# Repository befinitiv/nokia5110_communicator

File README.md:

# Contents

This repository contains Kicad PCB files and OpenSCAD mechanical parts to build a custom BLE keyboard.

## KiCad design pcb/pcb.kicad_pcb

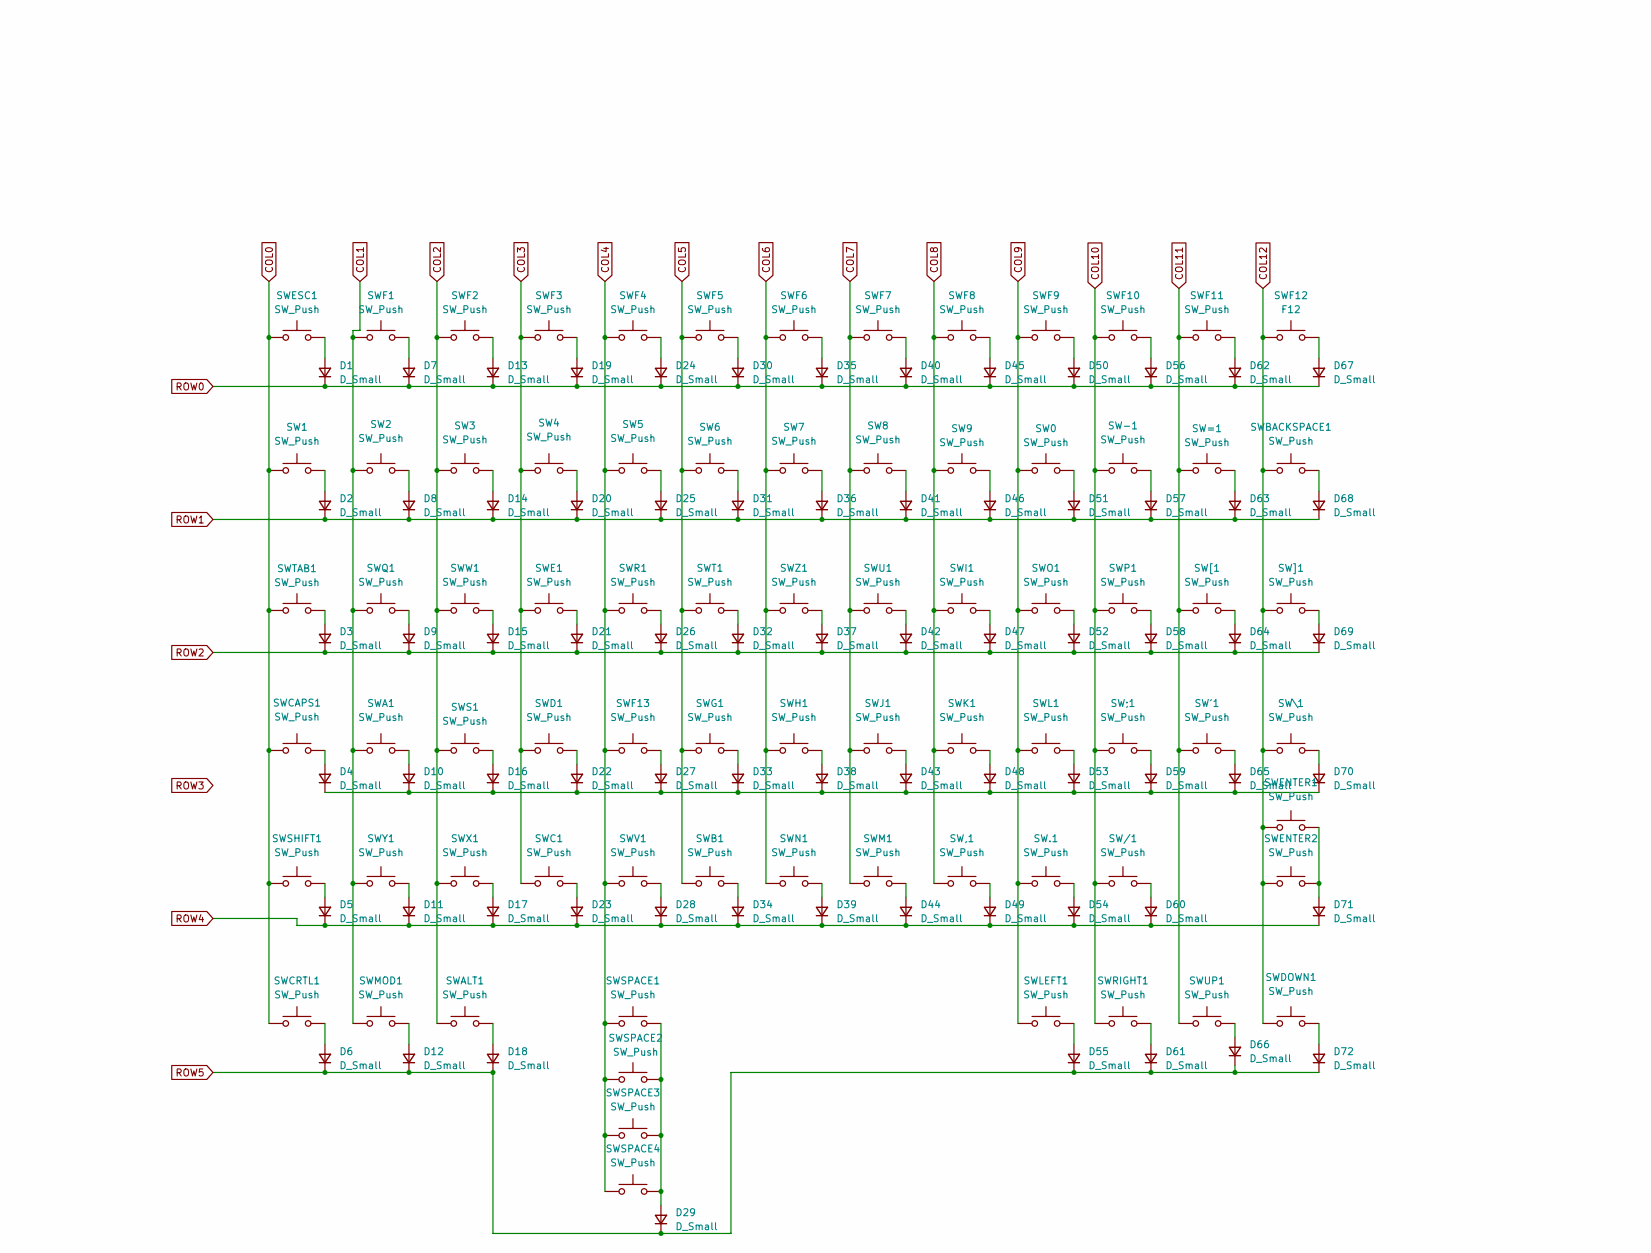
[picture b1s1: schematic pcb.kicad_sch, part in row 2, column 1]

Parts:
D1, D2, D3, D4, D5, D6, D7, D8, D9, D10, D11, D12, D13, D14, D15, D16, D17, D18, D19, D20, D21, D22, D23, D24, D25, D26, D27, D28, D29, D30, D31, D32, D33, D34, D35, D36, D37, D38, D39, D40, D41, D42, D43, D44, D45, D46, D47, D48, D49, D50, D51, D52, D53, D54, D55, D56, D57, D58, D59, D60, D61, D62, D63, D64, D65, D66, D67, D68, D69, D70, D71, D72: D_Small; D_0603_1608Metric_Pad1.05x0.95mm_HandSolder
SW0, SW1, SW2, SW3, SW4, SW5, SW6, SW7, SW8, SW9, SW.1: SW_Push; membrane_key
SW'1: SW_Push; membrane_key
SW,1: SW_Push; membrane_key
SW-1: SW_Push; membrane_key
SW/1: SW_Push; membrane_key
SW;1: SW_Push; membrane_key
SW=1: SW_Push; membrane_key
SWA1: SW_Push; membrane_key
SWALT1: SW_Push; membrane_key
SWB1: SW_Push; membrane_key
SWBACKSPACE1: SW_Push; membrane_key
SWC1: SW_Push; membrane_key
SWCAPS1: SW_Push; membrane_key
SWCRTL1: SW_Push; membrane_key
SWD1: SW_Push; membrane_key
SWDOWN1: SW_Push; membrane_key
SWE1: SW_Push; membrane_key
SWENTER1, SWENTER2: SW_Push; membrane_key
SWESC1: SW_Push; membrane_key
SWF1, SWF2, SWF3, SWF4, SWF5, SWF6, SWF7, SWF8, SWF9, SWF10, SWF11, SWF13: SW_Push; membrane_key
SWF12: F12; membrane_key
SWG1: SW_Push; membrane_key
SWH1: SW_Push; membrane_key
SWI1: SW_Push; membrane_key
SWJ1: SW_Push; membrane_key
SWK1: SW_Push; membrane_key
SWL1: SW_Push; membrane_key
SWLEFT1: SW_Push; membrane_key
SWM1: SW_Push; membrane_key
SWMOD1: SW_Push; membrane_key
SWN1: SW_Push; membrane_key
SWO1: SW_Push; membrane_key
SWP1: SW_Push; membrane_key
SWQ1: SW_Push; membrane_key
SWR1: SW_Push; membrane_key
SWRIGHT1: SW_Push; membrane_key
SWS1: SW_Push; membrane_key
SWSHIFT1: SW_Push; membrane_key
SWSPACE1, SWSPACE2, SWSPACE3, SWSPACE4: SW_Push; membrane_key
SWT1: SW_Push; membrane_key
SWTAB1: SW_Push; membrane_key
SWU1: SW_Push; membrane_key
SWUP1: SW_Push; membrane_key
SWV1: SW_Push; membrane_key
SWW1: SW_Push; membrane_key
SWX1: SW_Push; membrane_key
SWY1: SW_Push; membrane_key
SWZ1: SW_Push; membrane_key
SW[1: SW_Push; membrane_key
SW\1: SW_Push; membrane_key
SW]1: SW_Push; membrane_key

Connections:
COL0: SW1.1, SWCAPS1.1, SWCRTL1.1, SWESC1.1, SWSHIFT1.1, SWTAB1.1; also elsewhere on the board
COL1: SW2.1, SWA1.1, SWF1.1, SWMOD1.1, SWQ1.1, SWY1.1; also elsewhere on the board
COL2: SW3.1, SWALT1.1, SWF2.1, SWS1.1, SWW1.1, SWX1.1; also elsewhere on the board
COL3: SW4.1, SWC1.1, SWD1.1, SWE1.1, SWF3.1; also elsewhere on the board
COL4: SW5.1, SWF4.1, SWF13.1, SWR1.1, SWSPACE1.1, SWSPACE2.1, SWSPACE3.1, SWSPACE4.1, SWV1.1; also elsewhere on the board
COL5: SW6.1, SWB1.1, SWF5.1, SWG1.1, SWT1.1; also elsewhere on the board
COL6: SW7.1, SWF6.1, SWH1.1, SWN1.1, SWZ1.1; also elsewhere on the board
COL7: SW8.1, SWF7.1, SWJ1.1, SWM1.1, SWU1.1; also elsewhere on the board
COL8: SW9.1, SW,1.1, SWF8.1, SWI1.1, SWK1.1; also elsewhere on the board
COL9: SW0.1, SW.1.1, SWF9.1, SWL1.1, SWLEFT1.1, SWO1.1; also elsewhere on the board
COL10: SW-1.1, SW/1.1, SW;1.1, SWF10.1, SWP1.1, SWRIGHT1.1; also elsewhere on the board
COL11: SW'1.1, SW=1.1, SWF11.1, SWUP1.1, SW[1.1; also elsewhere on the board
COL12: SWBACKSPACE1.1, SWDOWN1.1, SWENTER1.1, SWENTER2.1, SWF12.1, SW\1.1, SW]1.1; also elsewhere on the board
unnamed: D4.1 (K), D10.1 (K), D16.1 (K), D22.1 (K), D27.1 (K), D33.1 (K), D38.1 (K), D43.1 (K), D48.1 (K), D53.1 (K), D59.1 (K), D65.1 (K), D70.1 (K)
unnamed: D51.2 (A), SW0.2
unnamed: D2.2 (A), SW1.2
unnamed: D8.2 (A), SW2.2
unnamed: D14.2 (A), SW3.2
unnamed: D20.2 (A), SW4.2
unnamed: D25.2 (A), SW5.2
unnamed: D31.2 (A), SW6.2
unnamed: D36.2 (A), SW7.2
unnamed: D41.2 (A), SW8.2
unnamed: D46.2 (A), SW9.2
unnamed: D65.2 (A), SW'1.2
unnamed: D49.2 (A), SW,1.2
unnamed: D57.2 (A), SW-1.2
unnamed: D54.2 (A), SW.1.2
unnamed: D60.2 (A), SW/1.2
unnamed: D59.2 (A), SW;1.2
unnamed: D63.2 (A), SW=1.2
unnamed: D10.2 (A), SWA1.2
unnamed: D18.2 (A), SWALT1.2
unnamed: D34.2 (A), SWB1.2
unnamed: D68.2 (A), SWBACKSPACE1.2
unnamed: D23.2 (A), SWC1.2
unnamed: D4.2 (A), SWCAPS1.2
unnamed: D6.2 (A), SWCRTL1.2
unnamed: D22.2 (A), SWD1.2
unnamed: D72.2 (A), SWDOWN1.2
unnamed: D21.2 (A), SWE1.2
unnamed: D71.2 (A), SWENTER1.2, SWENTER2.2
unnamed: D1.2 (A), SWESC1.2
unnamed: D7.2 (A), SWF1.2
unnamed: D13.2 (A), SWF2.2
unnamed: D19.2 (A), SWF3.2
unnamed: D24.2 (A), SWF4.2
unnamed: D30.2 (A), SWF5.2
unnamed: D35.2 (A), SWF6.2
unnamed: D40.2 (A), SWF7.2
unnamed: D45.2 (A), SWF8.2
unnamed: D50.2 (A), SWF9.2
unnamed: D56.2 (A), SWF10.2
unnamed: D62.2 (A), SWF11.2
unnamed: D67.2 (A), SWF12.2
unnamed: D27.2 (A), SWF13.2
unnamed: D33.2 (A), SWG1.2
unnamed: D38.2 (A), SWH1.2
unnamed: D47.2 (A), SWI1.2
unnamed: D43.2 (A), SWJ1.2
unnamed: D48.2 (A), SWK1.2
unnamed: D53.2 (A), SWL1.2
unnamed: D55.2 (A), SWLEFT1.2
unnamed: D44.2 (A), SWM1.2
unnamed: D12.2 (A), SWMOD1.2
unnamed: D39.2 (A), SWN1.2
unnamed: D52.2 (A), SWO1.2
unnamed: D58.2 (A), SWP1.2
unnamed: D9.2 (A), SWQ1.2
unnamed: D26.2 (A), SWR1.2
unnamed: D61.2 (A), SWRIGHT1.2
unnamed: D16.2 (A), SWS1.2
unnamed: D5.2 (A), SWSHIFT1.2
unnamed: D29.2 (A), SWSPACE1.2, SWSPACE2.2, SWSPACE3.2, SWSPACE4.2
unnamed: D32.2 (A), SWT1.2
unnamed: D3.2 (A), SWTAB1.2
unnamed: D42.2 (A), SWU1.2
unnamed: D66.2 (A), SWUP1.2
unnamed: D28.2 (A), SWV1.2
unnamed: D15.2 (A), SWW1.2
unnamed: D17.2 (A), SWX1.2
unnamed: D11.2 (A), SWY1.2
unnamed: D37.2 (A), SWZ1.2
unnamed: D64.2 (A), SW[1.2
unnamed: D70.2 (A), SW\1.2
unnamed: D69.2 (A), SW]1.2
ROW0: D1.1 (K), D7.1 (K), D13.1 (K), D19.1 (K), D24.1 (K), D30.1 (K), D35.1 (K), D40.1 (K), D45.1 (K), D50.1 (K), D56.1 (K), D62.1 (K), D67.1 (K); also elsewhere on the board
ROW1: D2.1 (K), D8.1 (K), D14.1 (K), D20.1 (K), D25.1 (K), D31.1 (K), D36.1 (K), D41.1 (K), D46.1 (K), D51.1 (K), D57.1 (K), D63.1 (K), D68.1 (K); also elsewhere on the board
ROW2: D3.1 (K), D9.1 (K), D15.1 (K), D21.1 (K), D26.1 (K), D32.1 (K), D37.1 (K), D42.1 (K), D47.1 (K), D52.1 (K), D58.1 (K), D64.1 (K), D69.1 (K); also elsewhere on the board
ROW4: D5.1 (K), D11.1 (K), D17.1 (K), D23.1 (K), D28.1 (K), D34.1 (K), D39.1 (K), D44.1 (K), D49.1 (K), D54.1 (K), D60.1 (K), D71.1 (K); also elsewhere on the board
ROW5: D6.1 (K), D12.1 (K), D18.1 (K), D29.1 (K), D55.1 (K), D61.1 (K), D66.1 (K), D72.1 (K); also elsewhere on the board

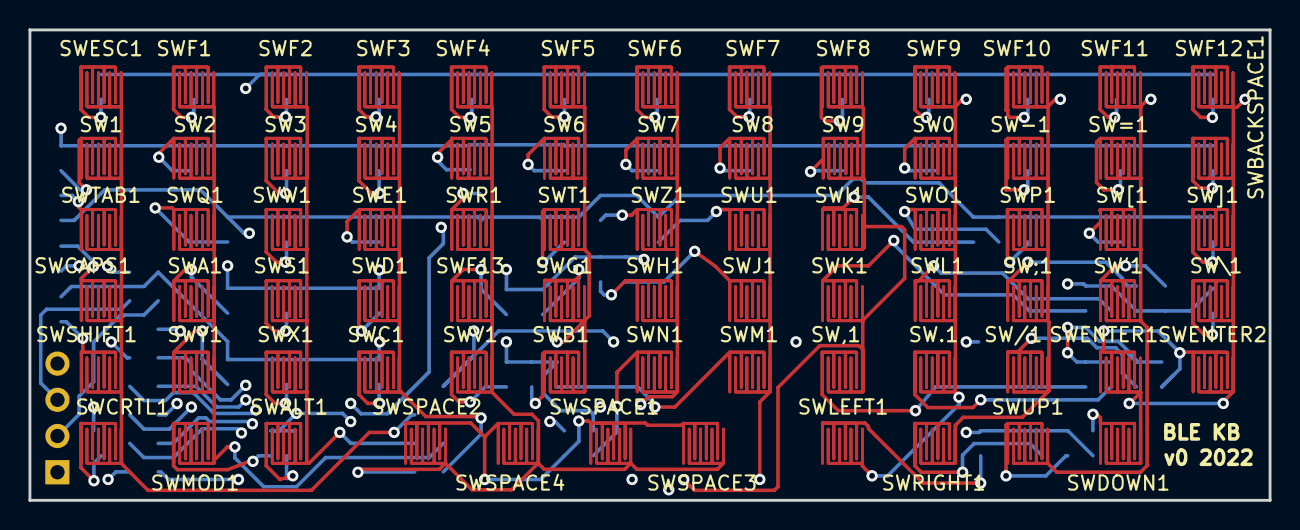
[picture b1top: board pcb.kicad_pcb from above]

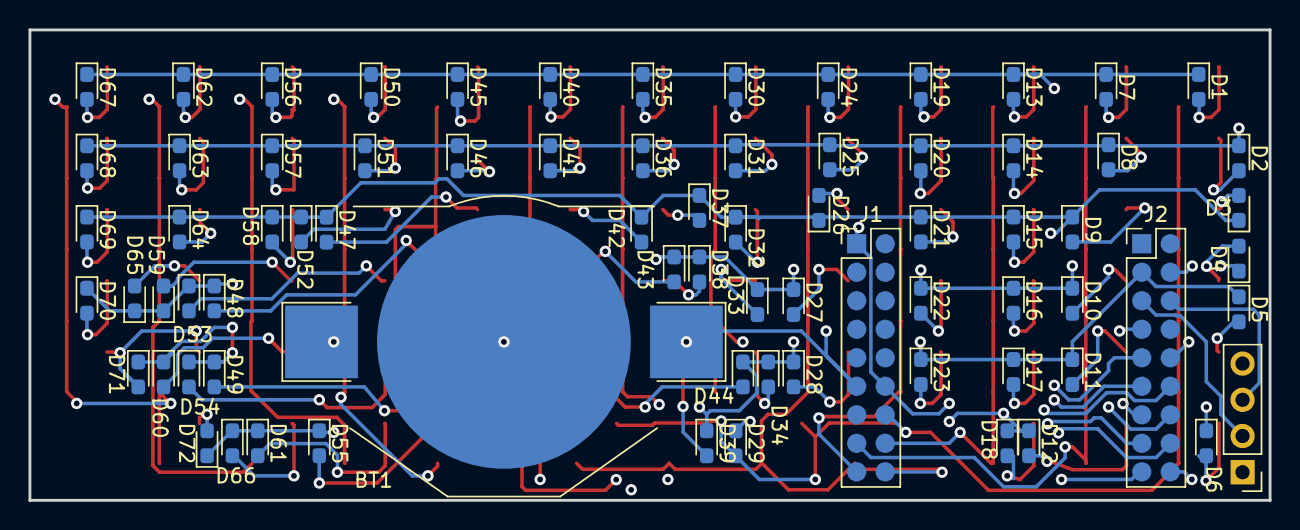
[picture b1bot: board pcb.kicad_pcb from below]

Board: 4 copper layers, 87.0 x 33.0 mm, 152 parts (76 on the bottom side), 95 nets.

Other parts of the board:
BT1: Battery_Cell; BatteryHolder_Keystone_3002_1x2032
J1, J2: Conn_02x09_Odd_Even; PinHeader_2x09_P2.00mm_Vertical
JDEBUG1: Conn_01x04; PinHeader_1x04_P2.54mm_Vertical

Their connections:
+3V0: BT1.1 (+), J1.11, JDEBUG1.4
COL0: J1.14; also elsewhere on the board
COL1: J1.15; also elsewhere on the board
COL2: J1.16; also elsewhere on the board
COL3: J1.17; also elsewhere on the board
COL4: J1.18; also elsewhere on the board
COL5: J2.17; also elsewhere on the board
COL6: J2.18; also elsewhere on the board
COL7: J2.15; also elsewhere on the board
COL8: J2.16; also elsewhere on the board
COL9: J2.13; also elsewhere on the board
COL10: J2.14; also elsewhere on the board
COL11: J2.11; also elsewhere on the board
COL12: J2.12; also elsewhere on the board
GND: BT1.2 (-), J1.1, J1.12, JDEBUG1.1
ROW0: J2.9; also elsewhere on the board
ROW1: J2.10; also elsewhere on the board
ROW2: J2.7; also elsewhere on the board
ROW4: J2.3; also elsewhere on the board
ROW5: J2.4; also elsewhere on the board
SWCLK: J2.6, JDEBUG1.3
SWD: J2.5, JDEBUG1.2

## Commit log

2022-05-02 PCB V0
2022-07-19 Mechanics working properly
2022-07-19 Added keymat SVG file
2022-07-19 Added readme
